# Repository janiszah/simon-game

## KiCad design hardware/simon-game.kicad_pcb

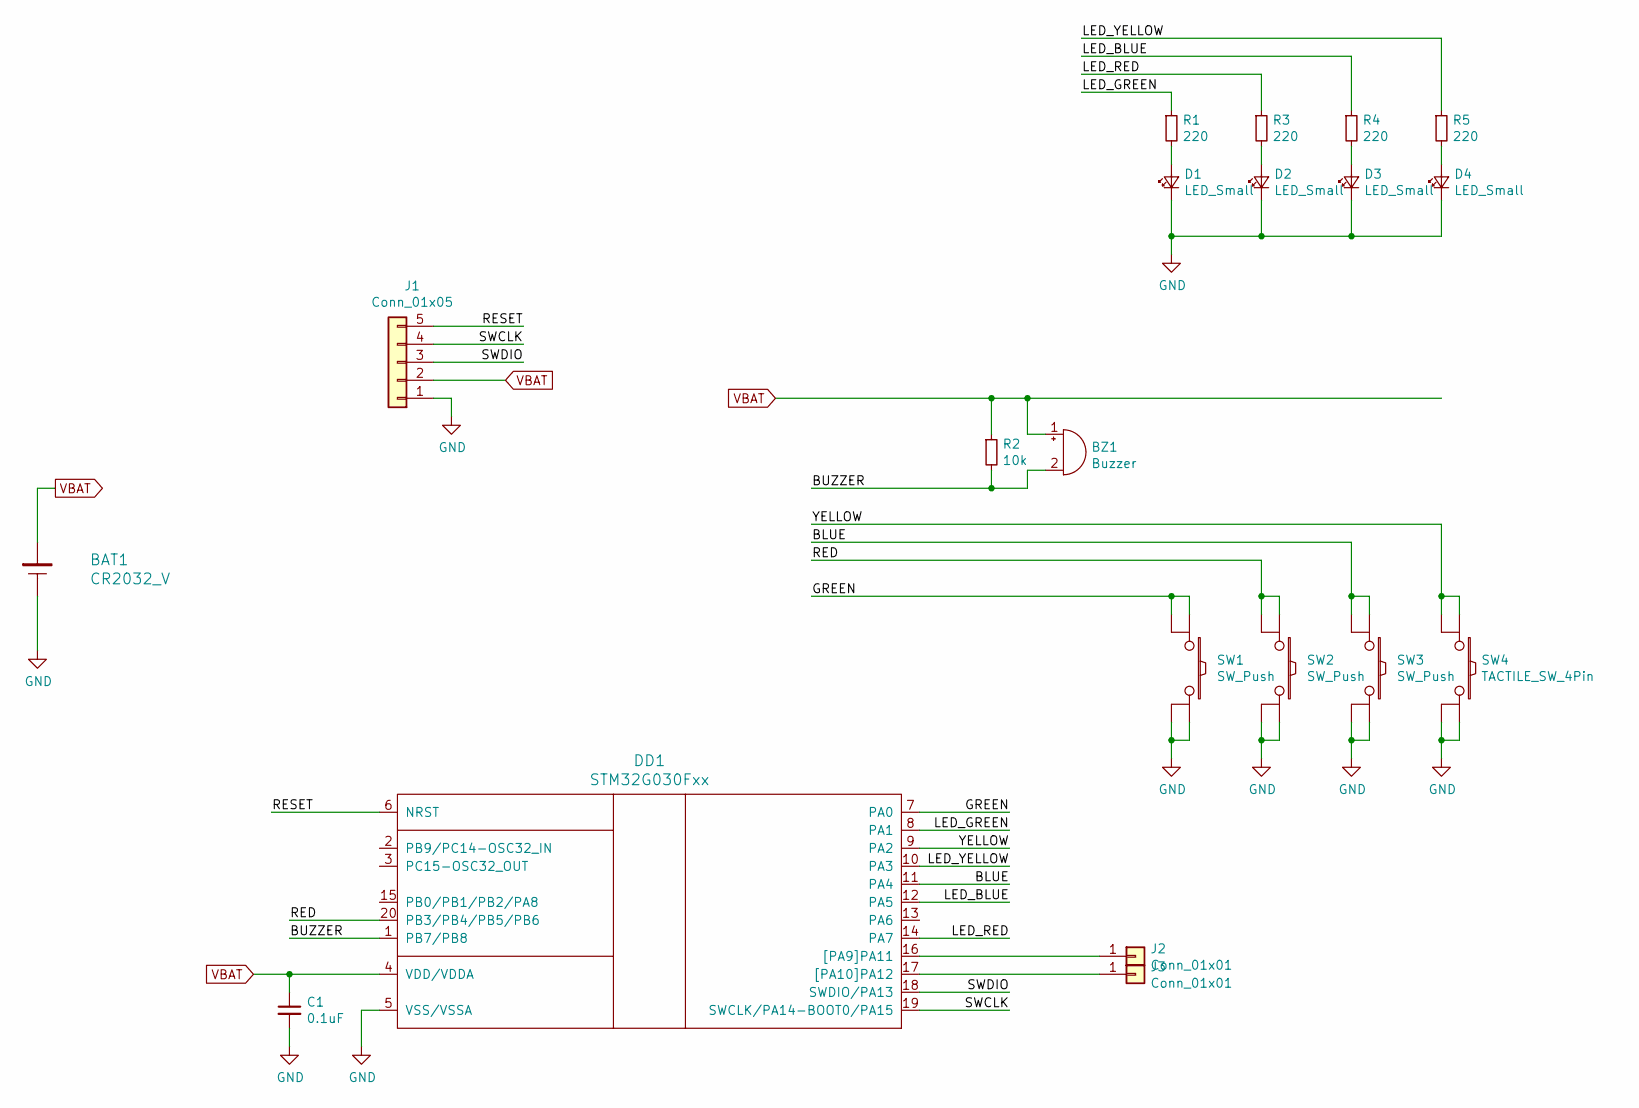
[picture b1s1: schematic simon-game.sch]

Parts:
BAT1: CR2032_V; BatteryHolder_Keystone_3002_1x2032
BZ1: Buzzer; Beeper_12xx
C1: 0.1uF; CE-2mm54
D1, D2, D3, D4: LED_Small; LED_D5.0mm
DD1: STM32G030Fxx; TSSOP-20_4.4x6.5mm_P0.65mm
J1: Conn_01x05; PinHeader_1x05_P2.54mm_Vertical
J2, J3: Conn_01x01; TestPoint_Pad_D2.0mm
R1, R3, R4, R5: 220; R_W8_THT_Hor
R2: 10k; R_W8_THT_Hor
SW1, SW2, SW3: SW_Push; 6x6_SPST
SW4: TACTILE_SW_4Pin; 6x6_SPST

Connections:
/BLUE: DD1.11 (PA4), SW3.1, SW3.2
/BUZZER: BZ1.2 (+), DD1.1 (PB7/PB8), R2.2
/GREEN: DD1.7 (PA0), SW1.1, SW1.2
/LED_BLUE: DD1.12 (PA5), R4.1
/LED_GREEN: DD1.8 (PA1), R1.1
/LED_RED: DD1.14 (PA7), R3.1
/LED_YELLOW: DD1.10 (PA3), R5.1
/RED: DD1.20 (PB3/PB4/PB5/PB6), SW2.1, SW2.2
/RESET: DD1.6 (NRST), J1.5
/SWCLK: DD1.19 (SWCLK/PA14-BOOT0/PA15), J1.4
/SWDIO: DD1.18 (SWDIO/PA13), J1.3
/YELLOW: DD1.9 (PA2), SW4.1, SW4.2
GND: BAT1.2, C1.2, D1.1 (K), D2.1 (K), D3.1 (K), D4.1 (K), DD1.5 (VSS/VSSA), J1.1, SW1.3, SW1.4, SW2.3, SW2.4, SW3.3, SW3.4, SW4.3, SW4.4
unnamed: D1.2 (A), R1.2
unnamed: D2.2 (A), R3.2
unnamed: D3.2 (A), R4.2
unnamed: D4.2 (A), R5.2
unnamed: DD1.16 ([PA9]PA11), J2.1
unnamed: DD1.17 ([PA10]PA12), J3.1
VBAT: BAT1.1, BZ1.1 (-), C1.1, DD1.4 (VDD/VDDA), J1.2, R2.1

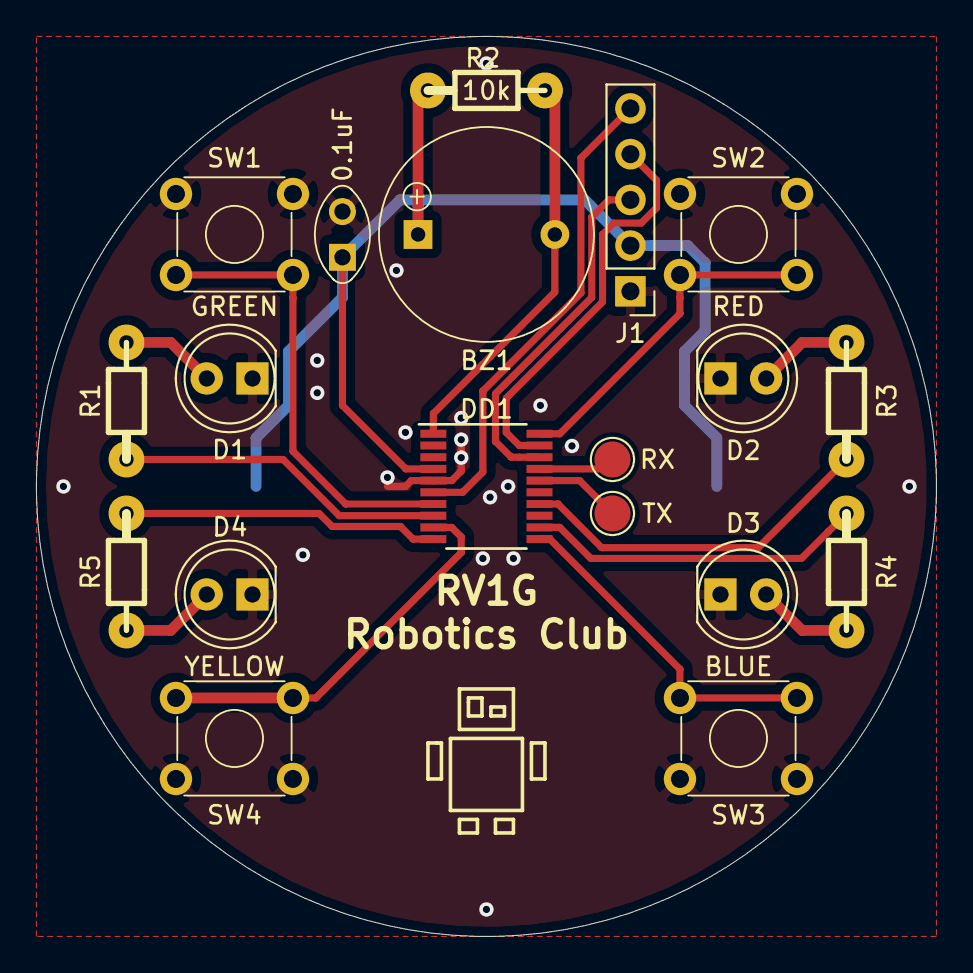
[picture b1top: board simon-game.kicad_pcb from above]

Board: 2 copper layers, 50.0 x 50.0 mm, 20 parts (1 on the bottom side), 20 nets.

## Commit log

2019-10-31 Working on PCB
2019-11-08 Finished PCB
2019-11-08 Fixed battery orientation
2019-12-18 Added Arduino sketch
2022-12-07 New STM32G030 based hardware
2022-12-07 STM32G0 project
2022-12-12 Hardware init
2023-11-12 Working on STM32G0
2023-11-12 Added hold to turn on and auto power off.
